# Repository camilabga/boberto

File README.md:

# Boberto: 2019 IEEE Open Competition Robot

Boberto was a robot developed by six students of LAR-UFRN (https://github.com/lar-ect). The competition consisted in proposing, developing and manufacturing a robot able to solve a portuary challenge.

2019 IEEE Open was a part of LARC (Latin American Robotics Competition) and happened in Rio Grande, RS, Brazil. The robot described here accomplished the second place, but is also currently the two-time Brazilian champion in the category.

The main goal was deposit as much containers as possible in a enviroment with a simulation of two ships (one blue and other green) and one train (red). Each container had a different pontuation. The team with the greatest score would win the challenge.

Boberto was able to:
1. Identify and advance to a container zone;
2. Choose a container to pick and check its color;
3. If it consisted in a Blue/Green container, grab it and go to the ship zone;
4. If it consisted in a Red container, ignore it and keep moving to the next pile;
5. Come back and do it all over again;

The official document of the competition can be found [here](http://www.cbrobotica.org/wp-content/uploads/OPEN2018_2019_en.pdf).

The students that composed the team of LAR-UFRN were:
* Álvaro Portela (https://github.com/alvaropfn)
* Camila Barbosa (https://github.com/camilabga)
* Gabriel Vantuil (https://github.com/GabrielVantuil)
* Luiz Felipe Santana (https://github.com/LuizFelipeLemon)
* Richardson Santiago (https://github.com/vanluwin)
* Wendell Alves (https://github.com/wendellalves)

## Using [PlatformIO Cli](http://docs.platformio.org/en/latest/)

* Installing

```console
user@computer:~$ sudo python -c "$(curl -fsSL https://raw.githubusercontent.com/platformio/platformio/develop/scripts/get-platformio.py)"
```

* Uploading the code

```console
user@computer:~/IEEE-2019 $ pio run -t upload --upload-port=/dev/ttyUSB0
```

## Arduino Mega Schema

## Boberto Pinout

### Stepper motor

| Port      | Pin     |
|:--------: |:-------:|
| Dir       | 52      |
| Step      | 50      |
| Enable    | 13      |

### H Bridge 1

| Port      | Pin     |
|:--------: |:-------:|
| Claw_DC 1 | 11      |
| Claw_DC 2 | 12      |
| Motor 2.1 | 9       |
| Motor 2.2 | 10      |

### H Bridge 2

| Port         | Pin     |
|:-----------: |:-------:|
| Back Left 2  | 7       |
| Back Left 1  | 8       |
| Back Right 2 | 6       |
| Back Right 1 | 5       |

### H Bridge 3

| Port          | Pin     |
|:-------------:|:-------:|
| Front Right 1 | 45      |
| Front Right 2 | 4       |
| Front Left 1  | 46      |
| Front Left 2  | 44      |

### Encoders

| Port       | Pin     |
|:----------:|:-------:|
| Back Left  | 3       |
| Back Right | 2       |
| Front Right| 18      |
| Front Left | 19      |

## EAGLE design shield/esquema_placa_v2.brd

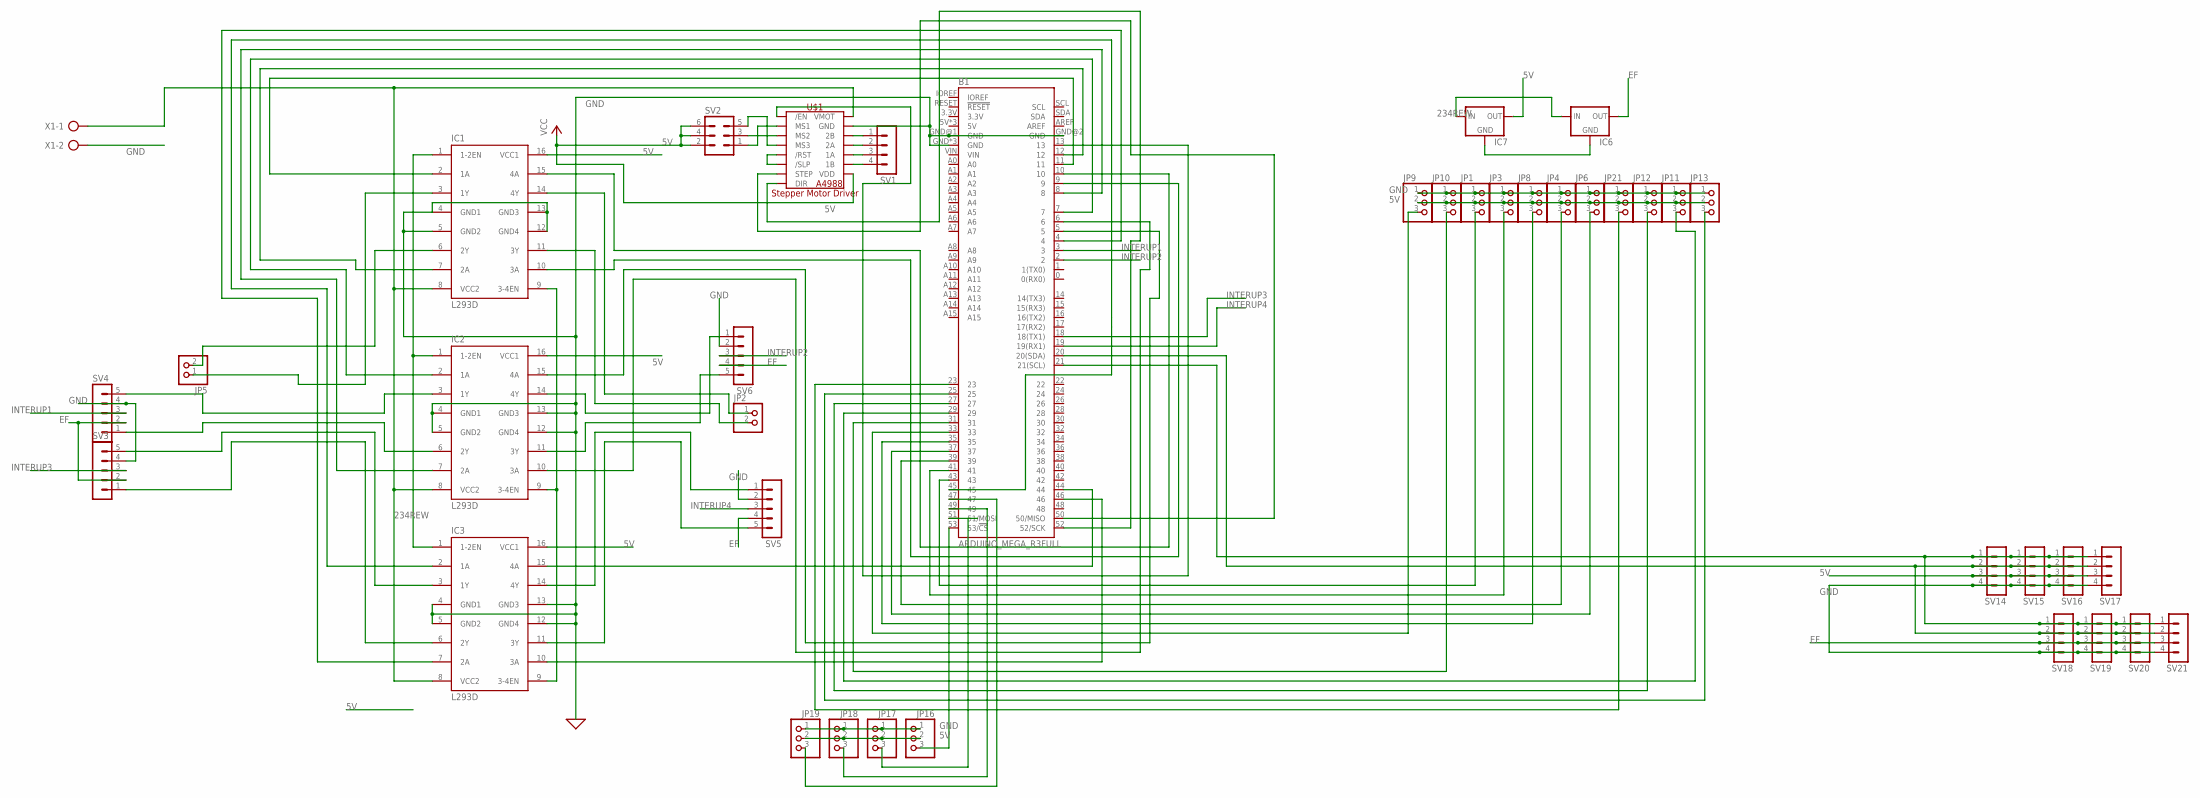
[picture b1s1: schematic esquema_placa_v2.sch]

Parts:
B1: ARDUINO_MEGA_R3FULL; ARDUINO_MEGA_NO_SILK
IC1, IC2, IC3: L293D; DIL16
IC6, IC7: 78XXS
JP1, JP3, JP4, JP6, JP8, JP9, JP10, JP11, JP12, JP13, JP16, JP17, JP18, JP19, JP21: PINHD-1X3; 1X03
JP2, JP5: PINHD-1X2; 1X02
SV1, SV14, SV15, SV16, SV17, SV18, SV19, SV20, SV21: MA04-1
SV2: MA03-2
SV3, SV4, SV5, SV6: MA05-1
U$1: A4988_STEP
X1: AK500/2-H

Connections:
5V: IC1.1 (1-2EN), IC1.9 (3-4EN), IC1.16 (VCC1), IC2.1 (1-2EN), IC2.9 (3-4EN), IC2.16 (VCC1), IC3.1 (1-2EN), IC3.9 (3-4EN), IC3.16 (VCC1), IC7.OUT, JP1.2, JP3.2, JP4.2, JP6.2, JP8.2, JP9.2, JP10.2, JP11.2, JP12.2, JP13.2, JP16.2, JP17.2, JP18.2, JP19.2, JP21.2, SV2.2, SV2.4, SV2.6, SV14.3, SV15.3, SV16.3, SV17.3, U$1.VDD
234REW: IC1.8 (VCC2), IC2.8 (VCC2), IC3.8 (VCC2), IC6.IN, IC7.IN, U$1.VMOT, X1.1
EF: IC6.OUT, SV3.2, SV4.2, SV5.4, SV6.4, SV18.3, SV19.3, SV20.3, SV21.3
GND: B1.GND, B1.GND@1 (GND), B1.GND@2 (GND), B1.GND@3 (GND), B1.GND@4 (GND), IC1.4 (GND1), IC1.5 (GND2), IC1.12 (GND4), IC1.13 (GND3), IC2.4 (GND1), IC2.5 (GND2), IC2.12 (GND4), IC2.13 (GND3), IC3.4 (GND1), IC3.5 (GND2), IC3.12 (GND4), IC3.13 (GND3), IC6.GND, IC7.GND, JP1.1, JP3.1, JP4.1, JP6.1, JP8.1, JP9.1, JP10.1, JP11.1, JP12.1, JP13.1, JP16.1, JP17.1, JP18.1, JP19.1, JP21.1, SV3.4, SV4.4, SV5.2, SV6.2, SV14.4, SV15.4, SV16.4, SV17.4, SV18.4, SV19.4, SV20.4, SV21.4, U$1.GND, U$1.GND2 (GND), X1.2
INTERUP1: B1.3, SV4.3
INTERUP2: B1.2, SV6.3
INTERUP3: B1.18 (18(TX1)), SV3.3
INTERUP4: B1.19 (19(RX1)), SV5.3
unnamed: B1.53 (53/!CS), JP16.3
unnamed: IC1.3 (1Y), JP5.1
unnamed: IC1.6 (2Y), JP5.2
unnamed: IC2.3 (1Y), SV4.5
unnamed: B1.45, IC3.2 (1A)
unnamed: IC2.6 (2Y), SV4.1
unnamed: IC3.3 (1Y), SV3.5
unnamed: IC3.6 (2Y), SV3.1
unnamed: IC2.14 (4Y), SV6.1
unnamed: IC2.11 (3Y), SV6.5
unnamed: IC3.14 (4Y), SV5.1
unnamed: IC3.11 (3Y), SV5.5
unnamed: IC1.11 (3Y), JP2.2
unnamed: IC1.14 (4Y), JP2.1
unnamed: B1.12, IC1.7 (2A)
unnamed: B1.11, IC1.2 (1A)
unnamed: B1.7, IC2.2 (1A)
unnamed: B1.8, IC2.7 (2A)
unnamed: B1.43, JP1.3
unnamed: B1.4, IC3.7 (2A)
unnamed: B1.10, IC1.15 (4A)
unnamed: B1.9, IC1.10 (3A)
unnamed: B1.5, IC2.15 (4A)
unnamed: B1.6, IC2.10 (3A)
unnamed: U$1./RST, U$1./SLP
unnamed: B1.46, IC3.10 (3A)
unnamed: B1.41, JP3.3
unnamed: SV1.1, U$1.2B
unnamed: SV1.2, U$1.2A
unnamed: SV1.3, U$1.1A
unnamed: SV1.4, U$1.1B
unnamed: SV2.3, U$1.MS2
unnamed: SV2.1, U$1.MS1
unnamed: SV2.5, U$1.MS3
unnamed: B1.44, IC3.15 (4A)
unnamed: B1.13, U$1./EN
unnamed: B1.50 (50/MISO), U$1.STEP
unnamed: B1.52 (52/SCK), U$1.DIR
unnamed: B1.39, JP4.3
unnamed: B1.51 (51/MOSI), JP17.3
unnamed: B1.49, JP18.3
unnamed: B1.47, JP19.3
unnamed: B1.37, JP6.3
unnamed: B1.35, JP8.3
unnamed: B1.33, JP9.3
unnamed: B1.31, JP10.3
unnamed: B1.29, JP11.3
unnamed: B1.27, JP12.3
unnamed: B1.25, JP13.3
unnamed: B1.20 (20(SDA)), SV14.2, SV15.2, SV16.2, SV17.2, SV18.2, SV19.2, SV20.2, SV21.2
unnamed: B1.23, JP21.3
unnamed: B1.21 (21(SCL)), SV14.1, SV15.1, SV16.1, SV17.1, SV18.1, SV19.1, SV20.1, SV21.1

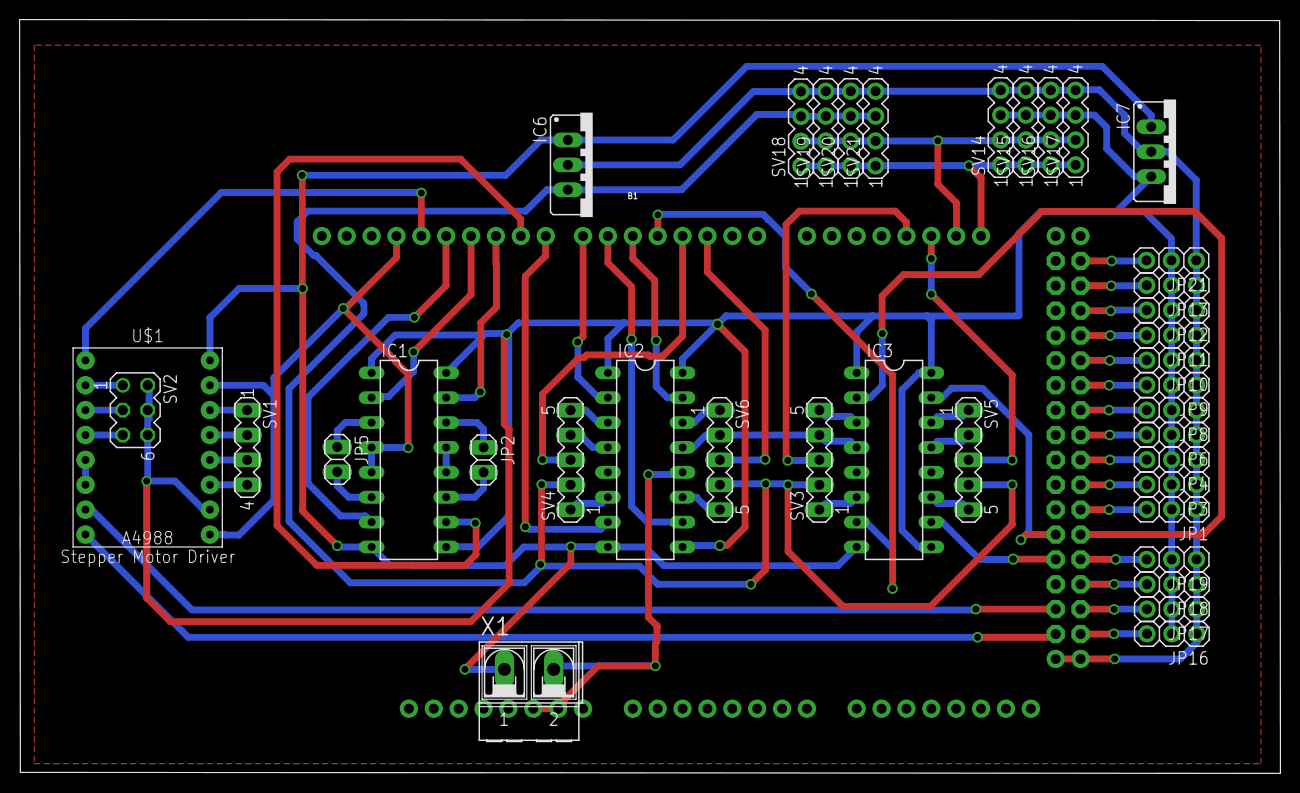
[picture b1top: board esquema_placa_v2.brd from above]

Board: 2 copper layers, 128.7 x 77.0 mm, 39 parts (0 on the bottom side), 60 nets.

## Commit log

2019-05-06 Classe para controle do robo
2019-05-06 Testes motor com encoder
2019-05-25 Pinout stuff
2019-05-25 link das regras
2019-06-01 PlatformIO tutorial
2019-06-01 Inicial code with interrupt
2019-06-01 Movimentation Funcs
2019-08-20 Movimentação
2019-08-24 Forward test
2019-08-24 Classe do motor com interrupt como método
2019-08-24 Classe do robo com os movimentos básicos
2019-08-24 Classe sensor criada; Métodos de movimentação adicionados; Primeiros métodos da maquina de estados;
2019-08-26 Classe da Garra
2019-08-31 Organizing branch
2019-08-31 Configs para arduino uno
2019-08-31 Classe do sensor de distancia
2019-08-31 Classe que encapsula o sensor de distancia
2019-08-31 Teste do sensor de distancia
2019-09-01 Métodos de movimentação funcionais. métodos de garra e elevador integrados.
2019-09-10 Documentação
2019-09-10 Classe do sensor de cor
2019-09-10 Funções de teste e integração com o sensor de cor
2019-09-10 Teste do sensor de cor
2019-09-14 Add button for robot config & color sensor calibr
2019-09-14 sucessfull import stockpile from a folder
2019-09-14 Corrected Ajust Time
2019-09-14 PWM reduction
2019-09-14 A lot of methods
2019-09-14 Ships movimentation
2019-09-15 finishing stockpile class
2019-09-15 moving class claw to dir claw
2019-09-15 refactory paths including folders
2019-09-16 followHorizontal working
2019-09-17 comandos motor travantes
2019-09-17 Ajuste nos tempos
2019-09-17 refactoring da classe
2019-09-17 coisas que não precisam estar aqui
2019-09-18 Line Sensor class refactoring
2019-09-18 Ajuste dos tempos
2019-09-18 Estrategi
2019-09-19 Add shield specification files
2019-09-19 Add necessary libraries for Eagle configuration
2019-09-28 Little bit of optimization
2019-09-28 New pins and stop condition
2019-09-28 removing .vscode from track
2019-09-28 really removing deleted folders
2019-09-28 adding documentation
2019-09-28 add routine and behaviors with color decisions for ships and containers
2019-09-28 merging with dev_container
2019-09-28 Fixing pins
2019-10-03 Baudrate maior
2019-10-03 Arena Stuff
2019-10-03 New Claw stuff
2019-10-03 DistanceSensor refactoring
2019-10-03 New pinout and movimentation
2019-10-03 Função para retornar a zona de containers
2019-10-03 Pegar dois containers
2019-10-05 Full Autonomus Mode
2019-10-11 alinhar com container com odometria
2019-10-11 Ignora a lina preta inicial
2019-10-11 Ir para a segunda pilha dos navios
2019-10-13 Novo sensor de cor do nosso lider
2019-10-13 Adaptando ao novo sensor de cor
2019-10-13 Algum teste ai
2019-10-15 final adjustments
2019-10-16 ajustes finos para sequencia de tarefas -- alinhar antes de pegar o container
2019-10-17 Sharpy and stuff
2019-10-18 New color sensor and claw
2019-10-19 Real full autonomus mode
2019-10-20 Lidando com o container vermelho
2019-10-23 Alinhar com navio
2019-10-23 ignorar vermelhos
2019-10-23 tentando alinhar no azul
2019-10-24 new alignWithShip
2019-10-24 Alguma merda com o followHorizontalLine ai
2019-10-28 And that was it

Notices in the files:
parts and their libraries:
Arduino: Licensing: Creative Commons ShareAlike 4.0 International - https://creativecommons.org/licenses/by-sa/4.0
